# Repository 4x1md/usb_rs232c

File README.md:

# USB to RS-232C adapter
USB to RS-232C adapter based on CH340G and MAX232 ICs.

## Overview

The adapter was designed for communcating with arbitrary waveform generators which have RS-232 interface.

It uses CH340G IC as a USB-to-UART adapter and MAX232 for converting 5V UART logic levels to RS-232.

The device can also be used as USB-to-UART adapter if MAX232 IC is not assembled. 

## Schematic

## BOM Variants

The device has two assembly options: USB to RS-232 adapter and USB to UART adapter.

### USB to RS-232 Adapter

### USB to UART Adapter

## PCB

## Photos

### RS-232 Assembly

### UART Assembly

## Links

1. [CH340G USB to RS232 TTL module schematic (D-SUN-V3.0)](http://nicecircuits.com/ch340g-usb-to-rs232-ttl-module-schematic-d-sun-v3-0/)
2. [Various modules from china - schematic reverse engineering etc.](https://github.com/NiceCircuits/modules_from_china)
3. [Микросхема CH340G – преобразователь интерфейса USB в UART (мост USB-UART). Характеристики, условия эксплуатации, типовые схемы включения](http://mypractic.ru/mikrosxema-ch340g-preobrazovatel-interfejsa-usb-v-uart-most-usb-uart-xarakteristiki-usloviya-ekspluatacii-tipovye-sxemy-vklyucheniya.html)

## Questions? Suggestions?
You are more than welcome to contact me with any questions, suggestions or propositions regarding this project. You can:

1. Visit [my QRZ.COM page](https://www.qrz.com/db/4X1MD)
2. Visit [my Facebook profile](https://www.facebook.com/Dima.Meln)
3. Write me an email to iosaaris =at= gmail dot com

## How to Support or Say Thanks

If you like this project, or found here some useful information and want to say thanks, or encourage me to do more, you can buy me a coffee!

You can aslo make a donation with PayPal:

---

**73 de 4X1MD**

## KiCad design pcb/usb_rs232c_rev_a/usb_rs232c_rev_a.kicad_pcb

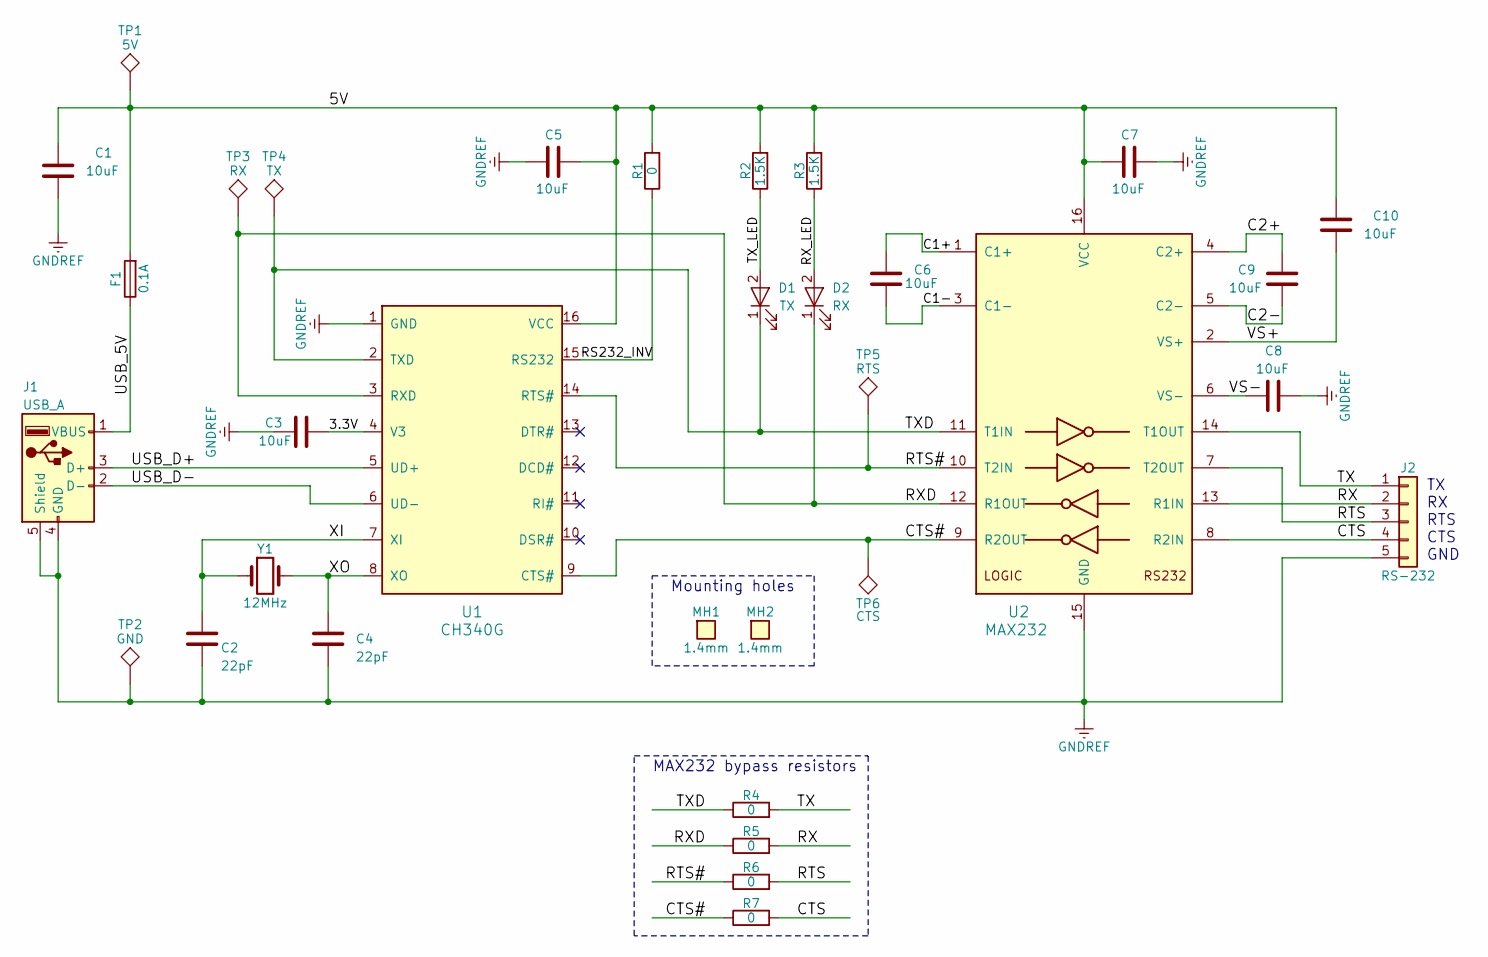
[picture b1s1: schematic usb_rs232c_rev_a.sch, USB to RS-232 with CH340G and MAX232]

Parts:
C1, C3, C5, C6, C7, C8, C9, C10: 10uF; C_0603
C2, C4: 22pF; C_0603
D1: TX; LED_0805
D2: RX; LED_0805
F1: 0.1A; Fuse_0603
J1: USB_A; USB_A_Male_THT
J2: RS-232; Pin_Header_Straight_1x05_Pitch2.54mm
MH1, MH2: 1.4mm; MountingHole_1.4mm
R1, R4, R5, R6, R7: 0; R_0603
R2, R3: 1.5K; R_0603
TP1: 5V; Measurement_Point_Square-SMD_1.0mmx1.0mm
TP2: GND; Measurement_Point_Square-SMD_1.0mmx1.0mm
TP3: RX; Measurement_Point_Square-SMD_1.0mmx1.0mm
TP4: TX; Measurement_Point_Square-SMD_1.0mmx1.0mm
TP5: RTS; Measurement_Point_Square-SMD_1.0mmx1.0mm
TP6: CTS; Measurement_Point_Square-SMD_1.0mmx1.0mm
U1: CH340G; SOIC-16_3.9x9.9mm_Pitch1.27mm
U2: MAX232; SOIC-16_3.9x9.9mm_Pitch1.27mm
Y1: 12MHz; Crystal_SMD_5032-2pin_5.0x3.2mm

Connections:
/3.3V: C3.2, U1.4 (V3)
/5V: C1.1, C5.1, C7.2, C10.1, F1.2, R1.2, R2.2, R3.2, TP1.1, U1.16 (VCC), U2.16 (VCC)
/C1+: C6.1, U2.1 (C1+)
/C1-: C6.2, U2.3 (C1-)
/C2+: C9.1, U2.4 (C2+)
/C2-: C9.2, U2.5 (C2-)
/CTS: J2.4, R7.2, U2.8 (R2IN)
/CTS#: R7.1, TP6.1, U1.9 (CTS#), U2.9 (R2OUT)
/RS232_INV: R1.1, U1.15 (RS232)
/RTS: J2.3, R6.2, U2.7 (T2OUT)
/RTS#: R6.1, TP5.1, U1.14 (RTS#), U2.10 (T2IN)
/RX: J2.2, R5.2, U2.13 (R1IN)
/RXD: D2.1 (K), R5.1, TP3.1, U1.3 (RXD), U2.12 (R1OUT)
/RX_LED: D2.2 (A), R3.1
/TX: J2.1, R4.2, U2.14 (T1OUT)
/TXD: D1.1 (K), R4.1, TP4.1, U1.2 (TXD), U2.11 (T1IN)
/TX_LED: D1.2 (A), R2.1
/USB_5V: F1.1, J1.1 (VBUS)
/USB_D+: J1.3 (D+), U1.5 (UD+)
/USB_D-: J1.2 (D-), U1.6 (UD-)
/VS+: C10.2, U2.2 (VS+)
/VS-: C8.2, U2.6 (VS-)
/XI: C2.1, U1.7 (XI), Y1.1
/XO: C4.1, U1.8 (XO), Y1.2
GNDREF: C1.2, C2.2, C3.1, C4.2, C5.2, C7.1, C8.1, J1.4 (GND), J1.5 (Shield), J2.5, TP2.1, U1.1 (GND), U2.15 (GND)

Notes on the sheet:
TX RX RTS CTS GND
Mounting holes
MAX232 bypass resistors

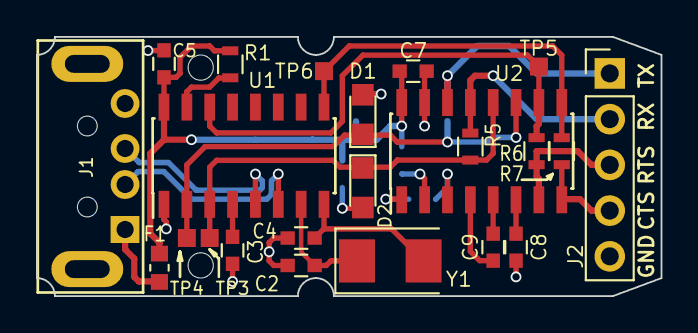
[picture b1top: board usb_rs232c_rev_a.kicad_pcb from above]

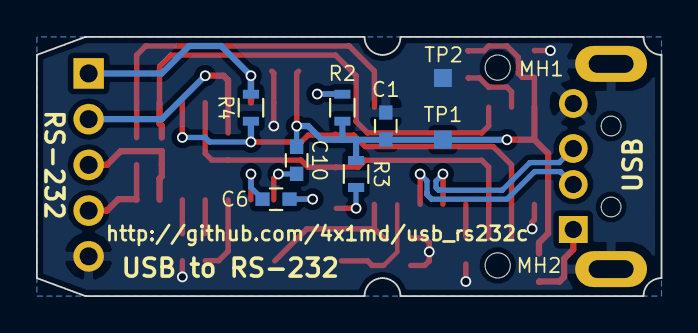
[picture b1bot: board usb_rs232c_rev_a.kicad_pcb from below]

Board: 2 copper layers, 34.7 x 14.4 mm, 33 parts (8 on the bottom side), 25 nets.

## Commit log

2018-03-24 PCB mechanical drawing.
2018-08-31 PCB production files.
2018-08-31 Readme and DXF.
2018-09-24 Updated PCB after the first iteration.
2018-10-01 3D model of PCB.
2018-10-01 schematic.png
2019-01-25 1. Added bypass resistors for MAX232. 2. Updated README.md
2019-03-23 README.md, images and .gitignore.
2019-03-23 Schematics update.
